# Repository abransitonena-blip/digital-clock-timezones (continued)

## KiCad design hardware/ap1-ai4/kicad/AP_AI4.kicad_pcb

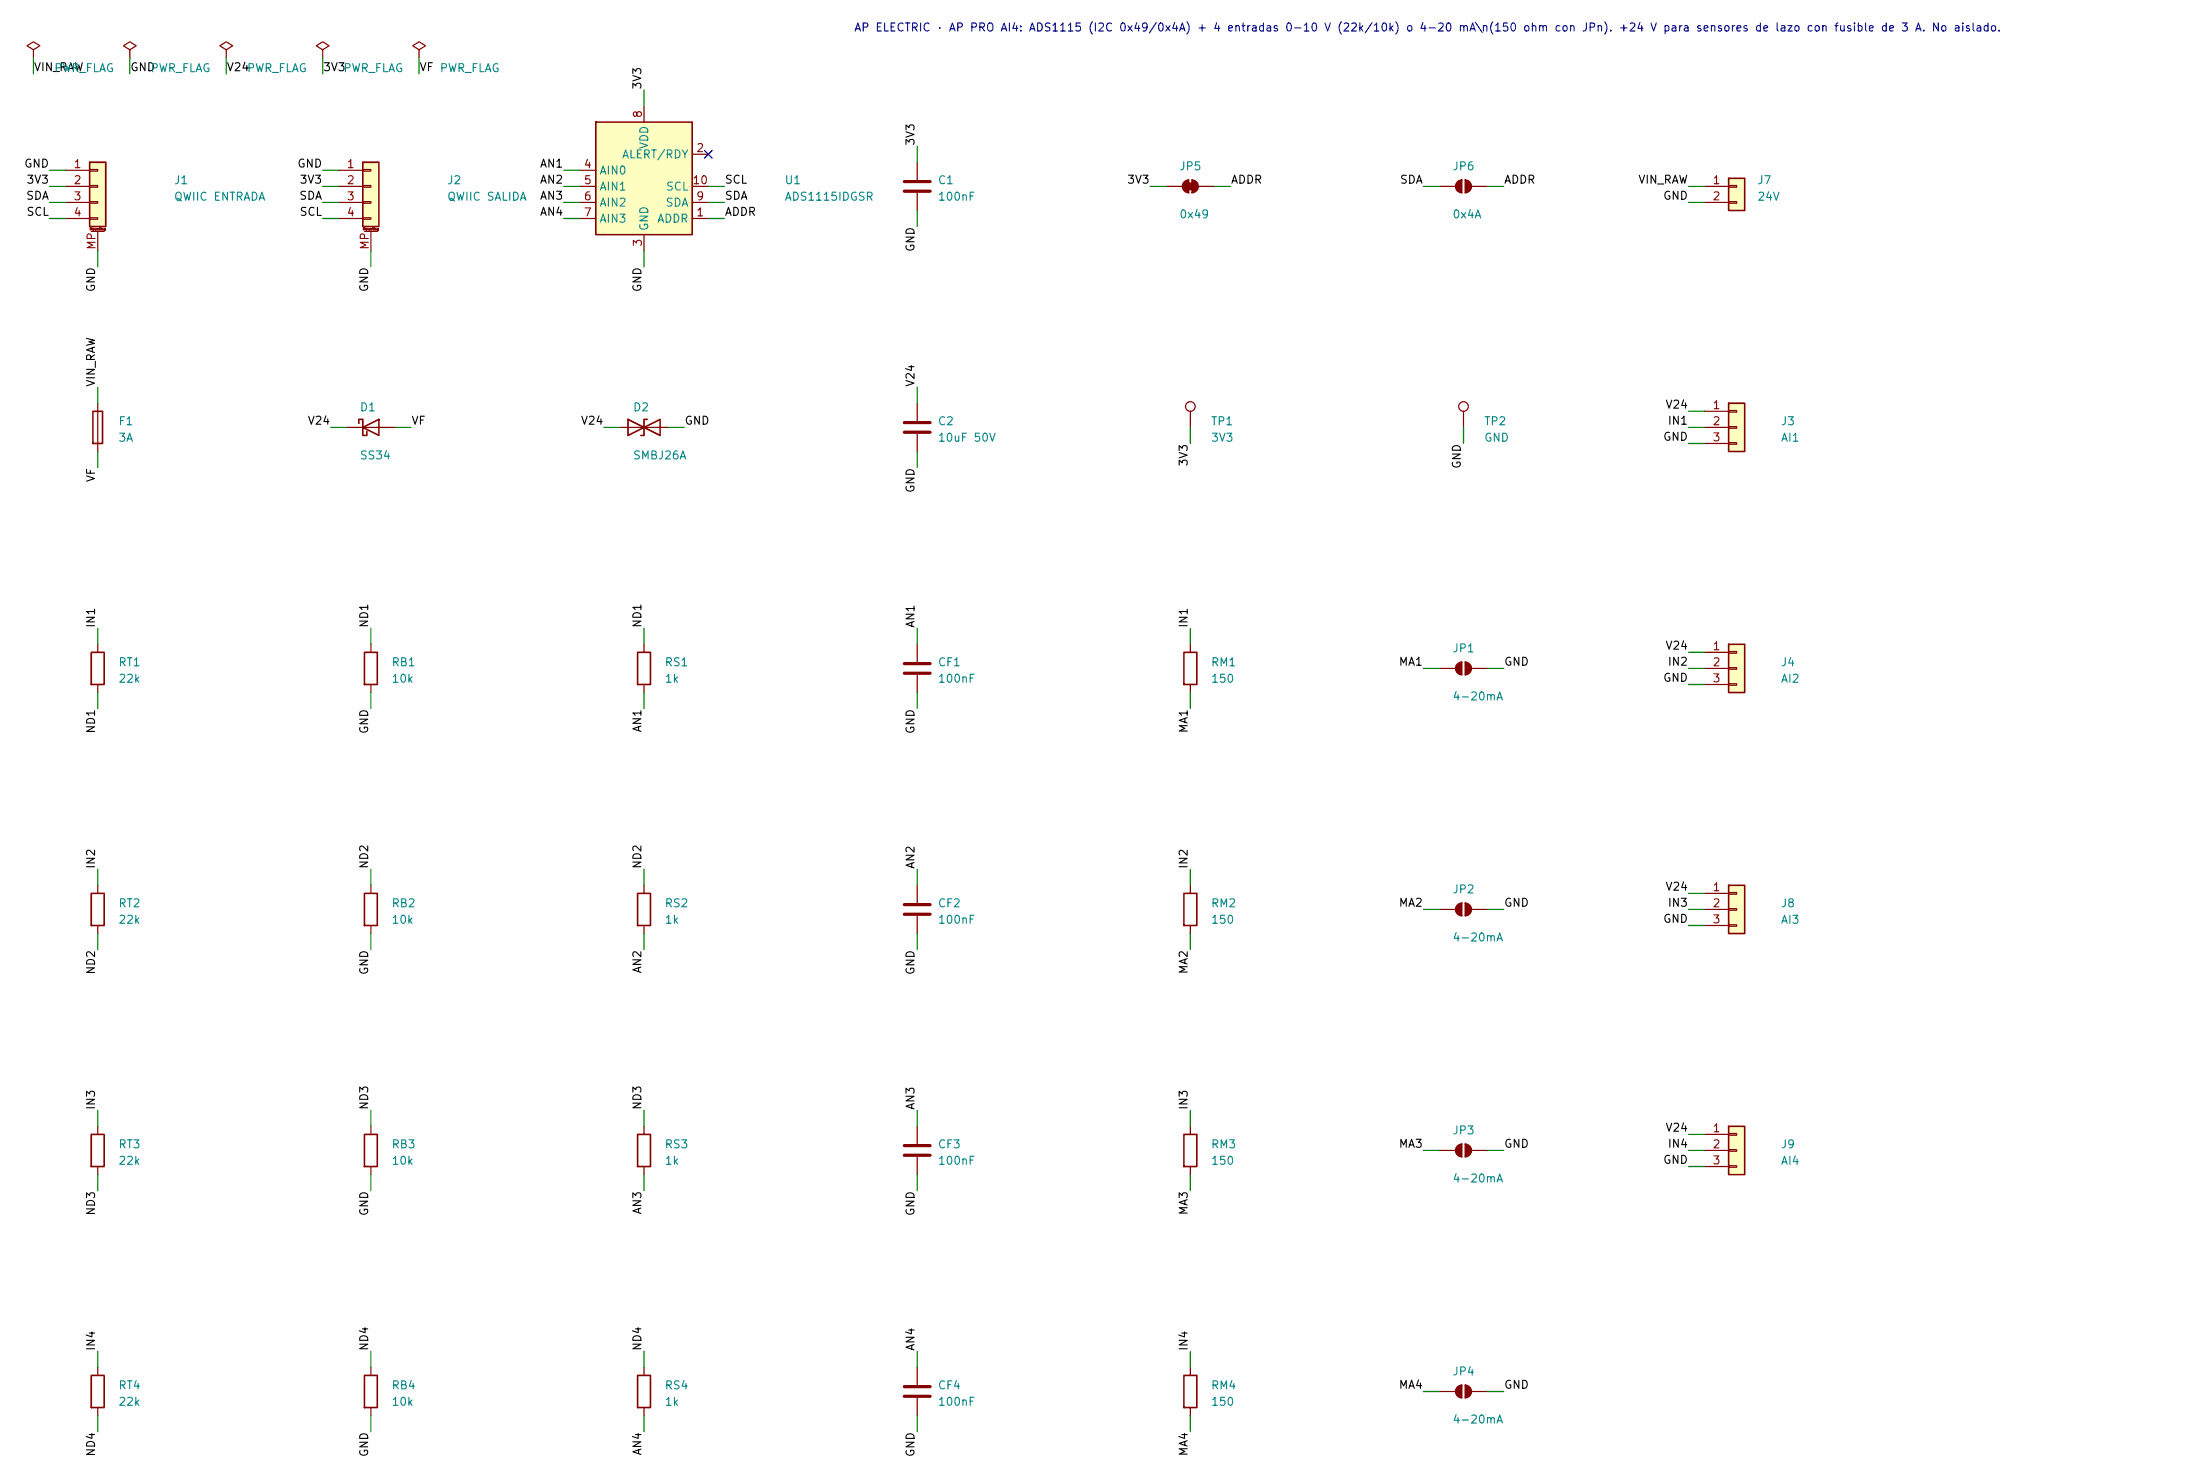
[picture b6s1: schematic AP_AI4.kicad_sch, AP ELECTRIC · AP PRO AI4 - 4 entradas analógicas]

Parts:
C1: 100nF; C_0603_1608Metric
C2: 10uF 50V; C_1206_3216Metric
CF1, CF2, CF3, CF4: 100nF; C_0603_1608Metric
D1: SS34; D_SMA
D2: SMBJ26A; D_SMB
F1: 3A; Fuse_1206_3216Metric
J1: QWIIC ENTRADA; JST_SH_SM04B-SRSS-TB_1x04-1MP_P1.00mm_Horizontal
J2: QWIIC SALIDA; JST_SH_SM04B-SRSS-TB_1x04-1MP_P1.00mm_Horizontal
J3: AI1; JST_XH_B3B-XH-A_1x03_P2.50mm_Vertical
J4: AI2; JST_XH_B3B-XH-A_1x03_P2.50mm_Vertical
J7: 24V; JST_VH_B2P-VH_1x02_P3.96mm_Vertical
J8: AI3; JST_XH_B3B-XH-A_1x03_P2.50mm_Vertical
J9: AI4; JST_XH_B3B-XH-A_1x03_P2.50mm_Vertical
JP1, JP2, JP3, JP4: 4-20mA; SolderJumper-2_P1.3mm_Open_RoundedPad1.0x1.5mm
JP5: 0x49; SolderJumper-2_P1.3mm_Bridged_RoundedPad1.0x1.5mm
JP6: 0x4A; SolderJumper-2_P1.3mm_Open_RoundedPad1.0x1.5mm
RB1, RB2, RB3, RB4: 10k; R_0603_1608Metric
RM1, RM2, RM3, RM4: 150; R_0805_2012Metric
RS1, RS2, RS3, RS4: 1k; R_0603_1608Metric
RT1, RT2, RT3, RT4: 22k; R_0603_1608Metric
TP1: 3V3; TestPoint_Pad_D1.5mm
TP2: GND; TestPoint_Pad_D1.5mm
U1: ADS1115IDGSR; TSSOP-10_3x3mm_P0.5mm

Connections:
/3V3: C1.1, J1.2, J2.2, JP5.1 (A), TP1.1, U1.8 (VDD)
/ADDR: JP5.2 (B), JP6.2 (B), U1.1 (ADDR)
/AN1: CF1.1, RS1.2, U1.4 (AIN0)
/AN2: CF2.1, RS2.2, U1.5 (AIN1)
/AN3: CF3.1, RS3.2, U1.6 (AIN2)
/AN4: CF4.1, RS4.2, U1.7 (AIN3)
/GND: C1.2, C2.2, CF1.2, CF2.2, CF3.2, CF4.2, D2.2 (A2), J1.1, J1.MP (MountPin), J2.1, J2.MP (MountPin), J3.3, J4.3, J7.2, J8.3, J9.3, JP1.2 (B), JP2.2 (B), JP3.2 (B), JP4.2 (B), RB1.2, RB2.2, RB3.2, RB4.2, TP2.1, U1.3 (GND)
/IN1: J3.2, RM1.1, RT1.1
/IN2: J4.2, RM2.1, RT2.1
/IN3: J8.2, RM3.1, RT3.1
/IN4: J9.2, RM4.1, RT4.1
/MA1: JP1.1 (A), RM1.2
/MA2: JP2.1 (A), RM2.2
/MA3: JP3.1 (A), RM3.2
/MA4: JP4.1 (A), RM4.2
/ND1: RB1.1, RS1.1, RT1.2
/ND2: RB2.1, RS2.1, RT2.2
/ND3: RB3.1, RS3.1, RT3.2
/ND4: RB4.1, RS4.1, RT4.2
/SCL: J1.4, J2.4, U1.10 (SCL)
/SDA: J1.3, J2.3, JP6.1 (A), U1.9 (SDA)
/V24: C2.1, D1.1 (K), D2.1 (A1), J3.1, J4.1, J8.1, J9.1
/VF: D1.2 (A), F1.2
/VIN_RAW: F1.1, J7.1

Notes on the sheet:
AP ELECTRIC · AP PRO AI4: ADS1115 (I2C 0x49/0x4A) + 4 entradas 0-10 V (22k/10k) o 4-20 mA\n(150 ohm con JPn). +24 V para sensores de lazo con fusible de 3 A. No aislado.

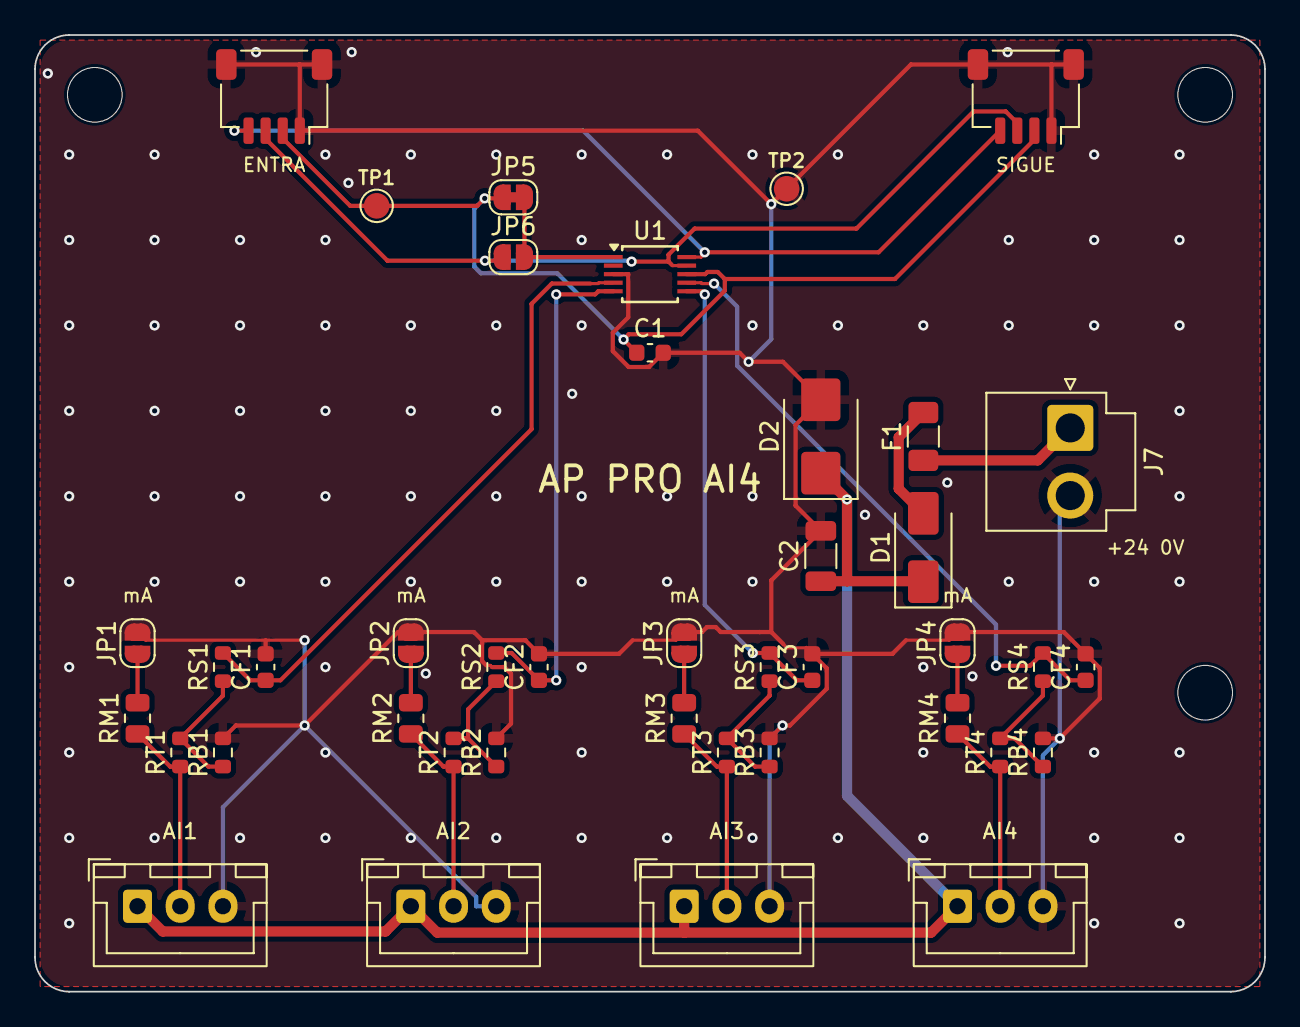
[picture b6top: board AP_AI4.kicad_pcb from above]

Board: 2 copper layers, 72.0 x 56.0 mm, 44 parts (0 on the bottom side), 24 nets.

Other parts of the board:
H1, H2, H3: MountingHole_3.2mm_M3

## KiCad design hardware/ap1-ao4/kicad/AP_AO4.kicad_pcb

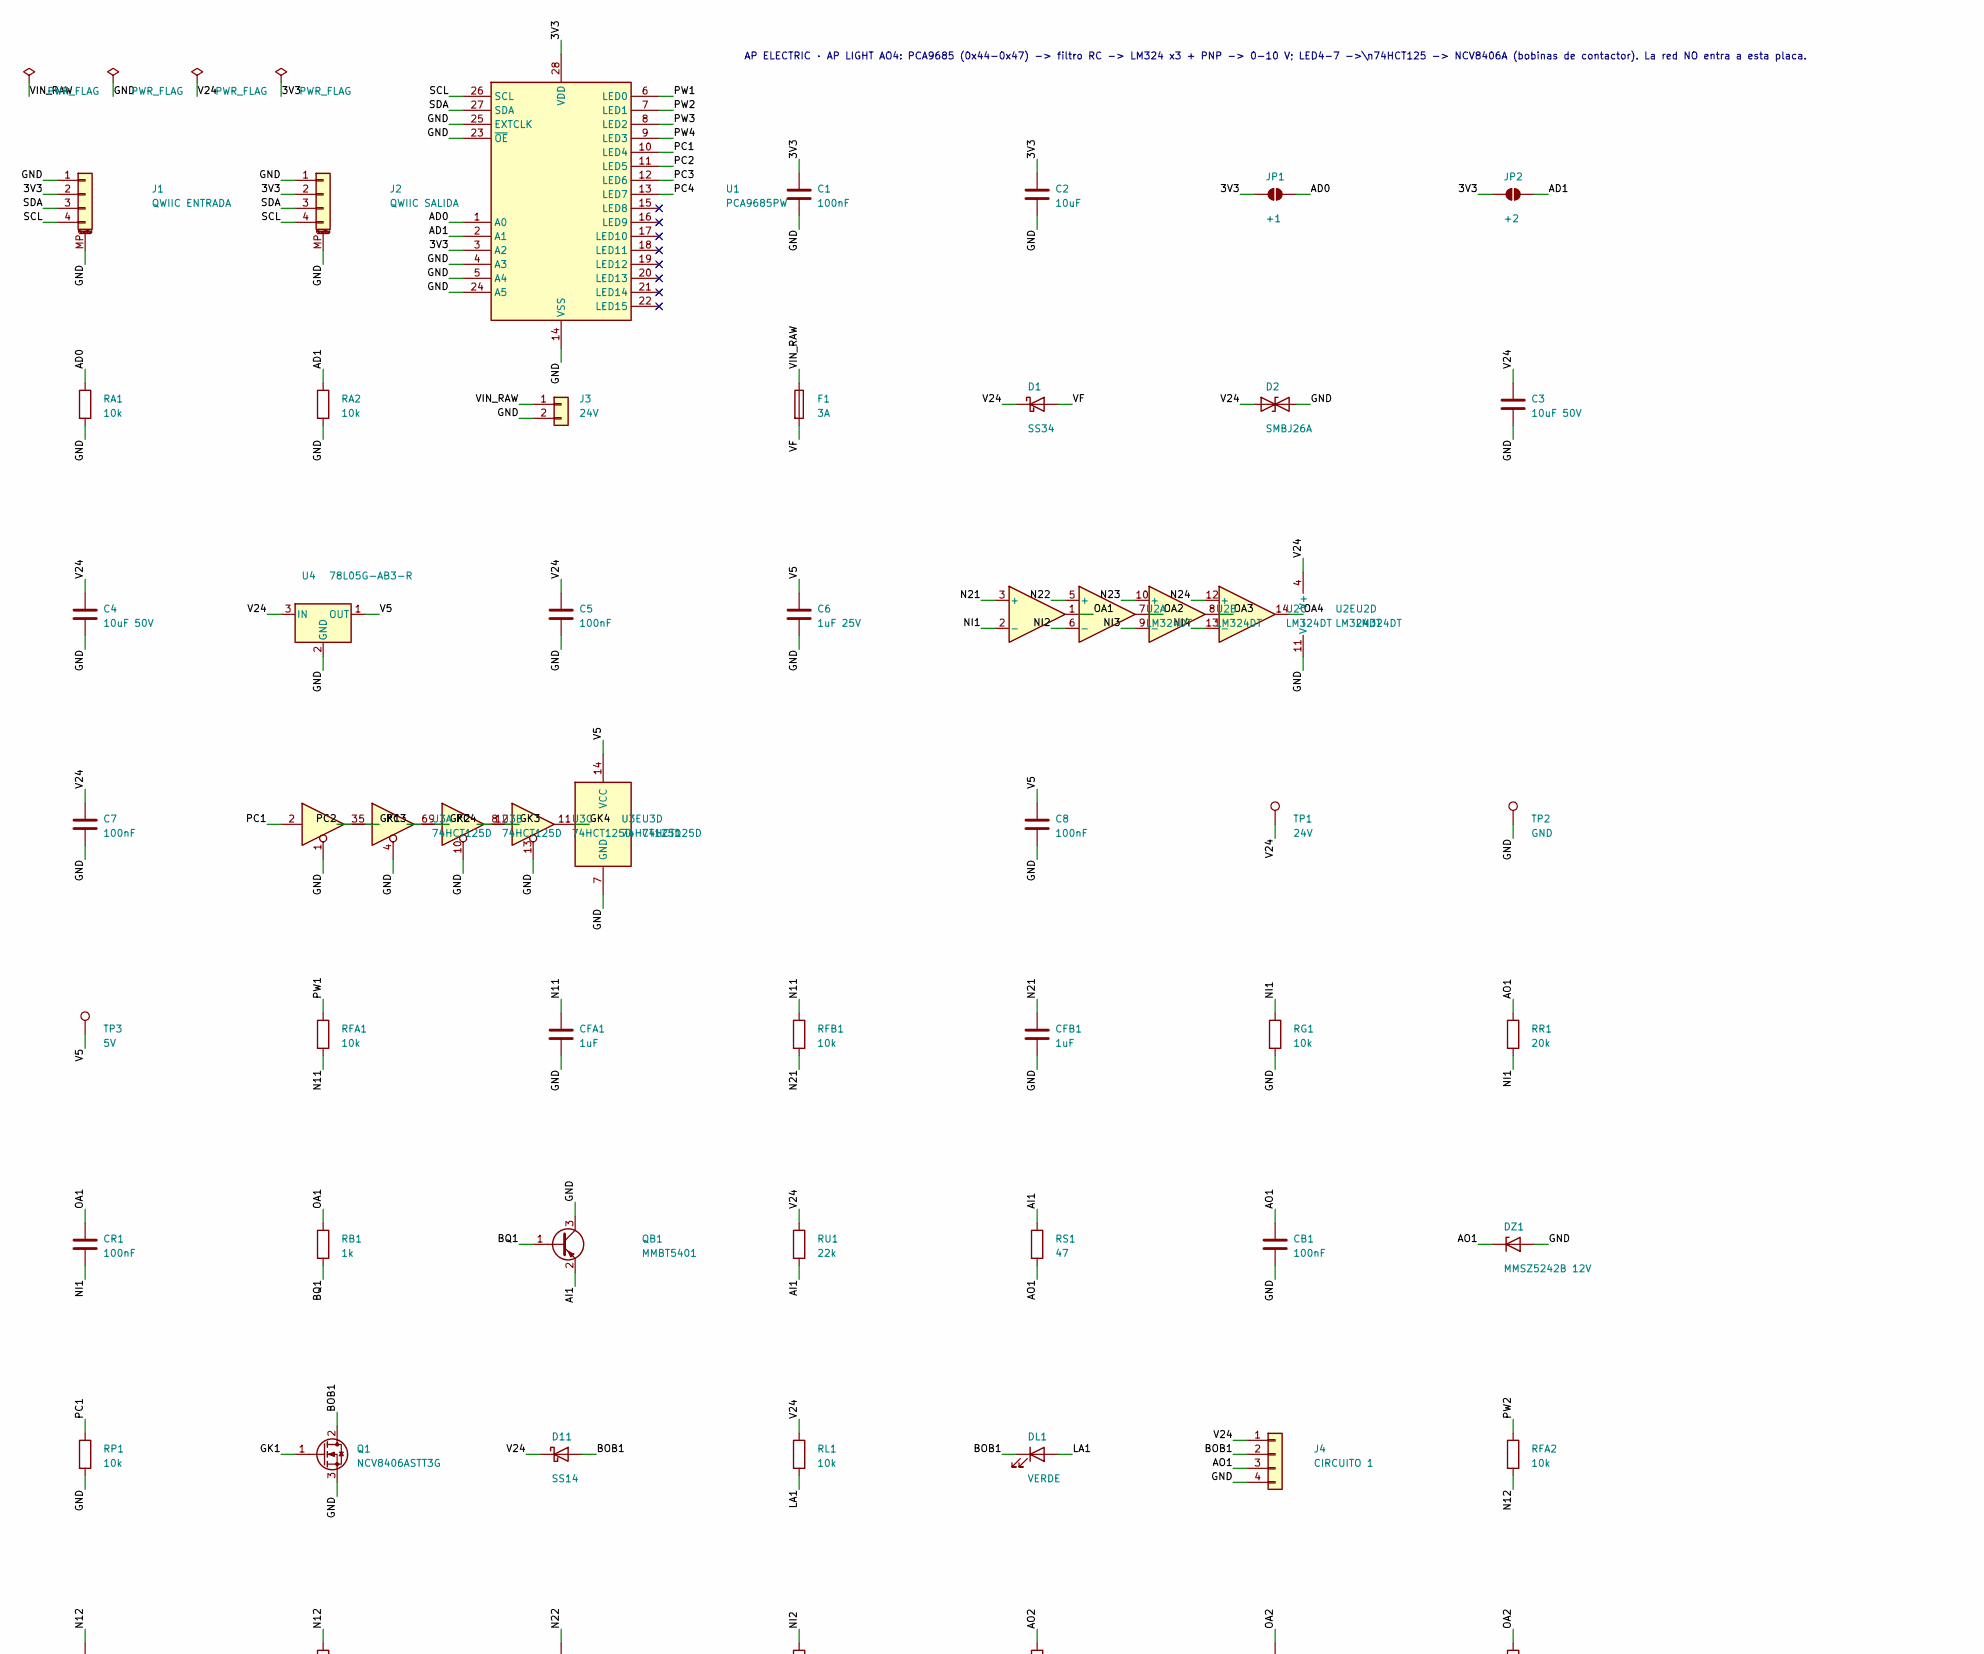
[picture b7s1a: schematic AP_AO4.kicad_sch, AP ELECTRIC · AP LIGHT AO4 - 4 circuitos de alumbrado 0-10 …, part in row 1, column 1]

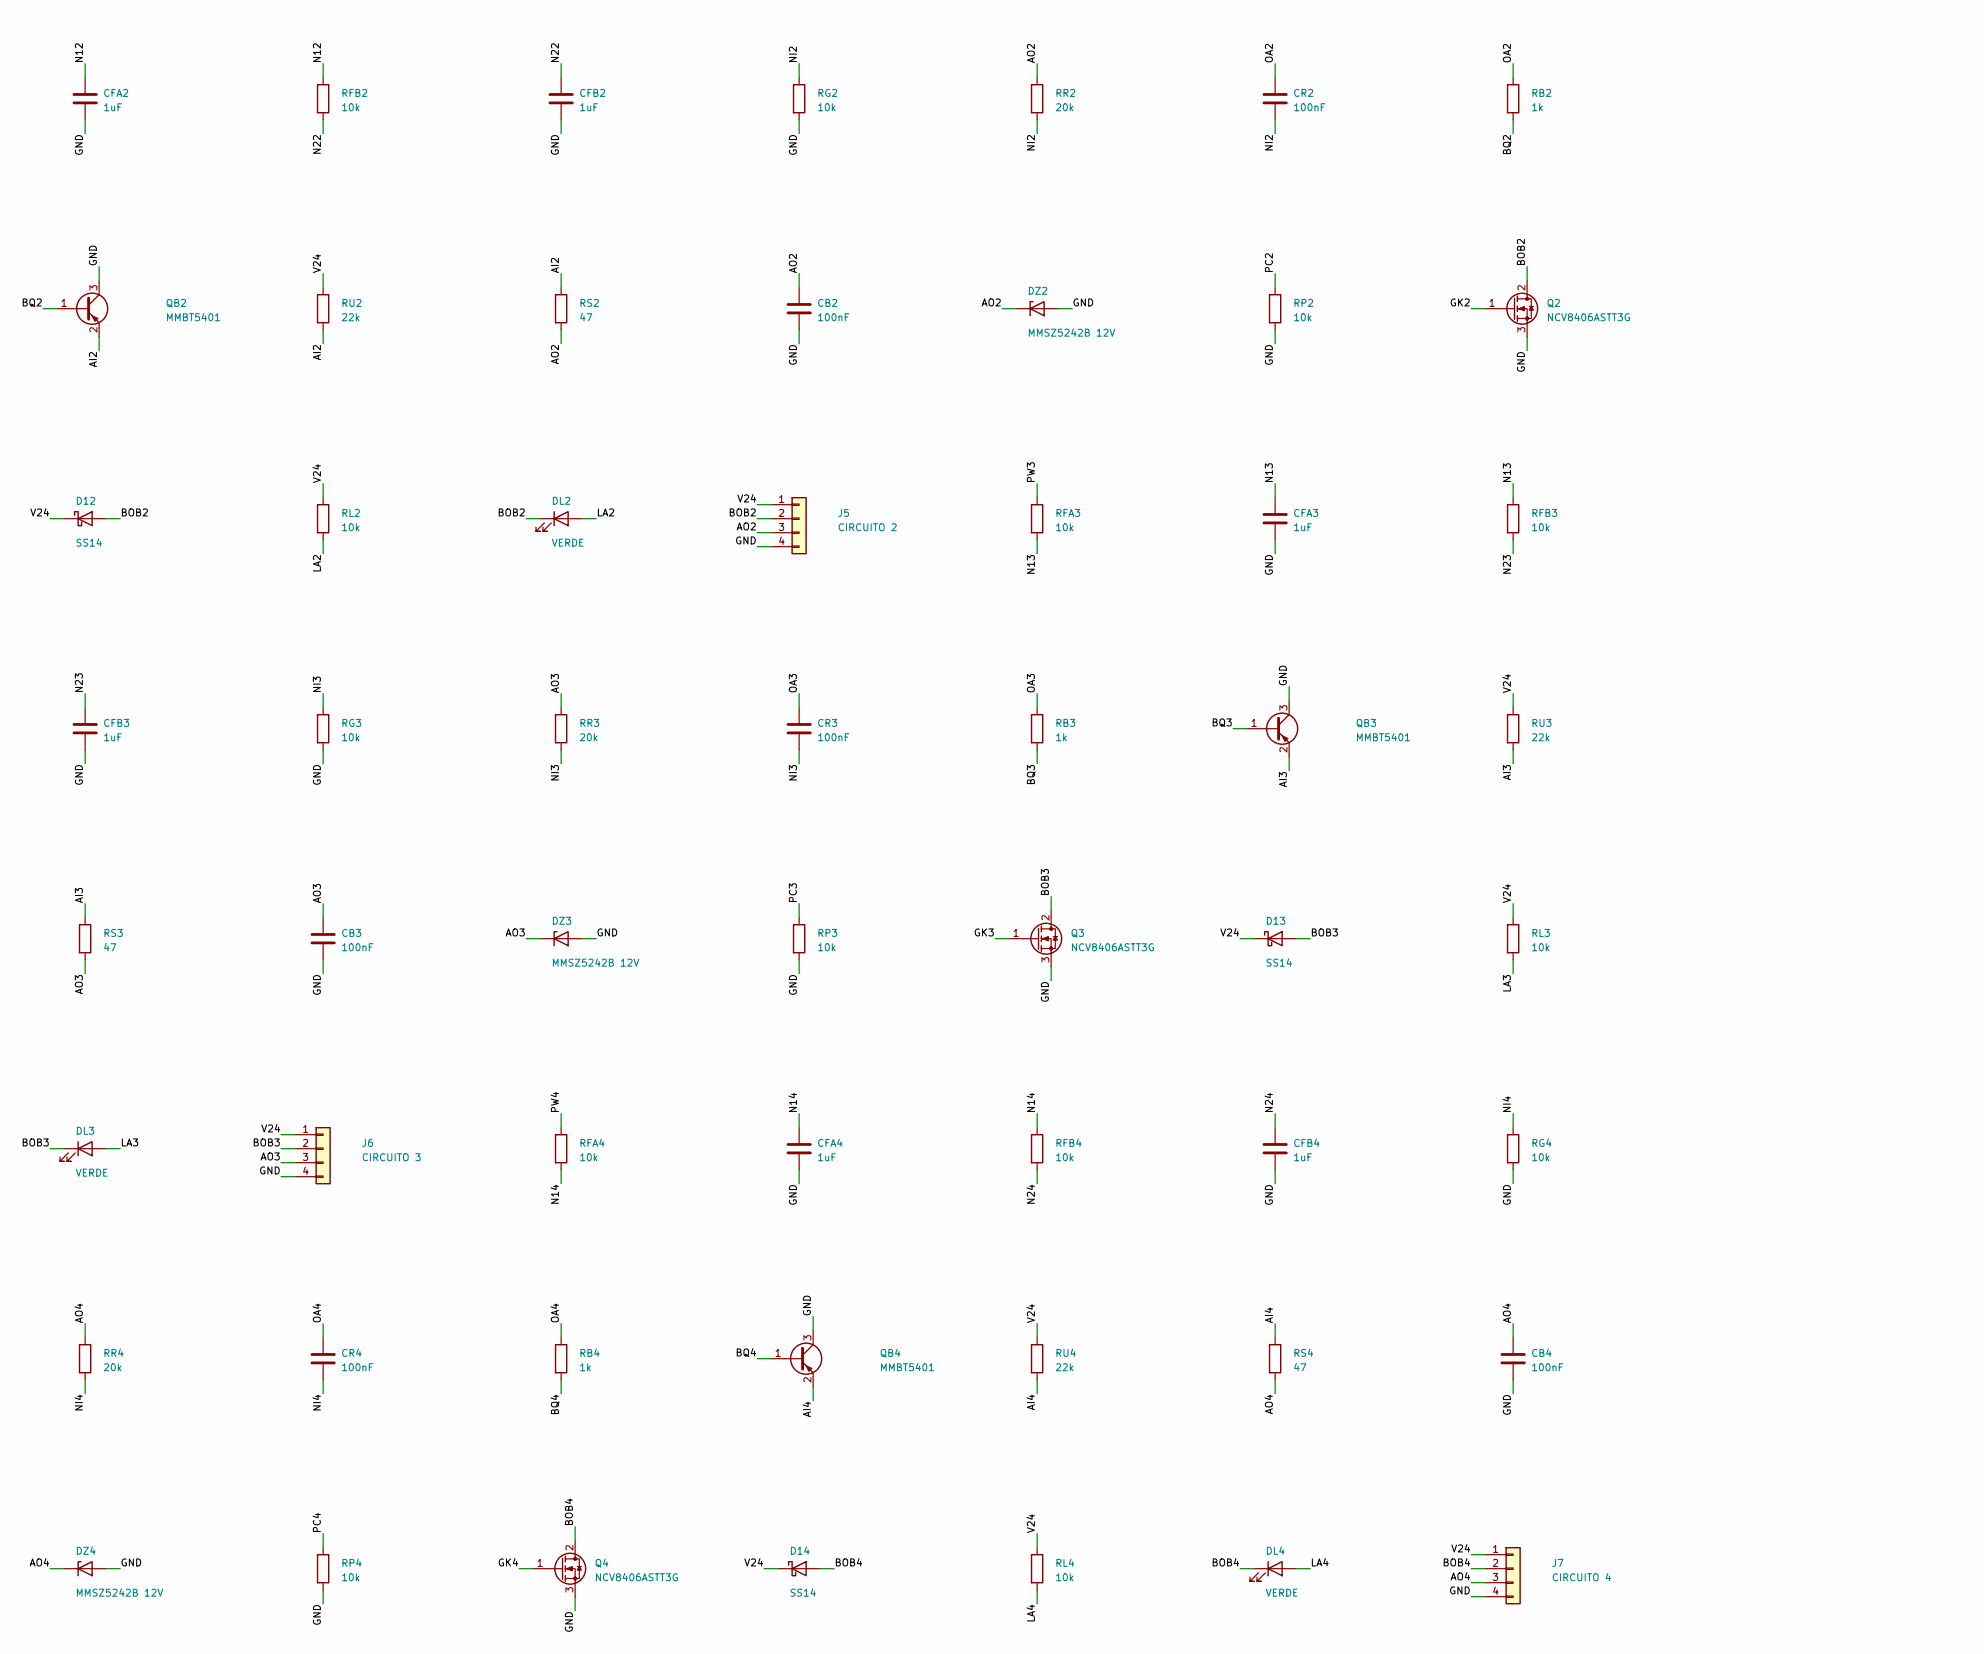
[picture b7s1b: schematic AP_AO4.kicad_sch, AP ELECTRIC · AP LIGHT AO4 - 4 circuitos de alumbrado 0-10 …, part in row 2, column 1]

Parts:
C1, C5, C7, C8: 100nF; C_0603_1608Metric
C2: 10uF; C_0805_2012Metric
C3, C4: 10uF 50V; C_1206_3216Metric
C6: 1uF 25V; C_0603_1608Metric
CB1, CB2, CB3, CB4: 100nF; C_0603_1608Metric
CFA1, CFA2, CFA3, CFA4: 1uF; C_0603_1608Metric
CFB1, CFB2, CFB3, CFB4: 1uF; C_0603_1608Metric
CR1, CR2, CR3, CR4: 100nF; C_0603_1608Metric
D1: SS34; D_SMA
D2: SMBJ26A; D_SMB
D11, D12, D13, D14: SS14; D_SMA
DL1, DL2, DL3, DL4: VERDE; LED_0603_1608Metric
DZ1, DZ2, DZ3, DZ4: MMSZ5242B 12V; D_SOD-123
F1: 3A; Fuse_1206_3216Metric
J1: QWIIC ENTRADA; JST_SH_SM04B-SRSS-TB_1x04-1MP_P1.00mm_Horizontal
J2: QWIIC SALIDA; JST_SH_SM04B-SRSS-TB_1x04-1MP_P1.00mm_Horizontal
J3: 24V; JST_VH_B2P-VH_1x02_P3.96mm_Vertical
J4: CIRCUITO 1; JST_XH_B4B-XH-A_1x04_P2.50mm_Vertical
J5: CIRCUITO 2; JST_XH_B4B-XH-A_1x04_P2.50mm_Vertical
J6: CIRCUITO 3; JST_XH_B4B-XH-A_1x04_P2.50mm_Vertical
J7: CIRCUITO 4; JST_XH_B4B-XH-A_1x04_P2.50mm_Vertical
JP1: +1; SolderJumper-2_P1.3mm_Open_RoundedPad1.0x1.5mm
JP2: +2; SolderJumper-2_P1.3mm_Open_RoundedPad1.0x1.5mm
Q1, Q2, Q3, Q4: NCV8406ASTT3G; SOT-223-3_TabPin2
QB1, QB2, QB3, QB4: MMBT5401; SOT-23
RA1, RA2: 10k; R_0603_1608Metric
RB1, RB2, RB3, RB4: 1k; R_0603_1608Metric
RFA1, RFA2, RFA3, RFA4: 10k; R_0603_1608Metric
RFB1, RFB2, RFB3, RFB4: 10k; R_0603_1608Metric
RG1, RG2, RG3, RG4: 10k; R_0603_1608Metric
RL1, RL2, RL3, RL4: 10k; R_0603_1608Metric
RP1, RP2, RP3, RP4: 10k; R_0603_1608Metric
RR1, RR2, RR3, RR4: 20k; R_0603_1608Metric
RS1, RS2, RS3, RS4: 47; R_0603_1608Metric
RU1, RU2, RU3, RU4: 22k; R_0603_1608Metric
TP1: 24V; TestPoint_Pad_D1.5mm
TP2: GND; TestPoint_Pad_D1.5mm
TP3: 5V; TestPoint_Pad_D1.5mm
U1: PCA9685PW; TSSOP-28_4.4x9.7mm_P0.65mm
U2: LM324DT; SOIC-14_3.9x8.7mm_P1.27mm
U3: 74HCT125D; SOIC-14_3.9x8.7mm_P1.27mm
U4: 78L05G-AB3-R; SOT-89-3

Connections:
/3V3: C1.1, C2.1, J1.2, J2.2, JP1.1 (A), JP2.1 (A), U1.3 (A2), U1.28 (VDD)
/AD0: JP1.2 (B), RA1.1, U1.1 (A0)
/AD1: JP2.2 (B), RA2.1, U1.2 (A1)
/AI1: QB1.2 (E), RS1.1, RU1.2
/AI2: QB2.2 (E), RS2.1, RU2.2
/AI3: QB3.2 (E), RS3.1, RU3.2
/AI4: QB4.2 (E), RS4.1, RU4.2
/AO1: CB1.1, DZ1.1 (K), J4.3, RR1.1, RS1.2
/AO2: CB2.1, DZ2.1 (K), J5.3, RR2.1, RS2.2
/AO3: CB3.1, DZ3.1 (K), J6.3, RR3.1, RS3.2
/AO4: CB4.1, DZ4.1 (K), J7.3, RR4.1, RS4.2
/BOB1: D11.2 (A), DL1.1 (K), J4.2, Q1.2 (D)
/BOB2: D12.2 (A), DL2.1 (K), J5.2, Q2.2 (D)
/BOB3: D13.2 (A), DL3.1 (K), J6.2, Q3.2 (D)
/BOB4: D14.2 (A), DL4.1 (K), J7.2, Q4.2 (D)
/BQ1: QB1.1 (B), RB1.2
/BQ2: QB2.1 (B), RB2.2
/BQ3: QB3.1 (B), RB3.2
/BQ4: QB4.1 (B), RB4.2
/GK1: Q1.1 (G), U3.3
/GK2: Q2.1 (G), U3.6
/GK3: Q3.1 (G), U3.8
/GK4: Q4.1 (G), U3.11
/GND: C1.2, C2.2, C3.2, C4.2, C5.2, C6.2, C7.2, C8.2, CB1.2, CB2.2, CB3.2, CB4.2, CFA1.2, CFA2.2, CFA3.2, CFA4.2, CFB1.2, CFB2.2, CFB3.2, CFB4.2, D2.2 (A2), DZ1.2 (A), DZ2.2 (A), DZ3.2 (A), DZ4.2 (A), J1.1, J1.MP (MountPin), J2.1, J2.MP (MountPin), J3.2, J4.4, J5.4, J6.4, J7.4, Q1.3 (S), Q2.3 (S), Q3.3 (S), Q4.3 (S), QB1.3 (C), QB2.3 (C), QB3.3 (C), QB4.3 (C), RA1.2, RA2.2, RG1.2, RG2.2, RG3.2, RG4.2, RP1.2, RP2.2, RP3.2, RP4.2, TP2.1, U1.4 (A3), U1.5 (A4), U1.14 (VSS), U1.23 (~OE), U1.24 (A5), U1.25 (EXTCLK), U2.11 (V-), U3.1, U3.4, U3.7 (GND), U3.10, U3.13, U4.2 (GND)
/LA1: DL1.2 (A), RL1.2
/LA2: DL2.2 (A), RL2.2
/LA3: DL3.2 (A), RL3.2
/LA4: DL4.2 (A), RL4.2
/N11: CFA1.1, RFA1.2, RFB1.1
/N12: CFA2.1, RFA2.2, RFB2.1
/N13: CFA3.1, RFA3.2, RFB3.1
/N14: CFA4.1, RFA4.2, RFB4.1
/N21: CFB1.1, RFB1.2, U2.3 (+)
/N22: CFB2.1, RFB2.2, U2.5 (+)
/N23: CFB3.1, RFB3.2, U2.10 (+)
/N24: CFB4.1, RFB4.2, U2.12 (+)
/NI1: CR1.2, RG1.1, RR1.2, U2.2 (-)
/NI2: CR2.2, RG2.1, RR2.2, U2.6 (-)
/NI3: CR3.2, RG3.1, RR3.2, U2.9 (-)
/NI4: CR4.2, RG4.1, RR4.2, U2.13 (-)
/OA1: CR1.1, RB1.1, U2.1
/OA2: CR2.1, RB2.1, U2.7
/OA3: CR3.1, RB3.1, U2.8
/OA4: CR4.1, RB4.1, U2.14
/PC1: RP1.1, U1.10 (LED4), U3.2
/PC2: RP2.1, U1.11 (LED5), U3.5
/PC3: RP3.1, U1.12 (LED6), U3.9
/PC4: RP4.1, U1.13 (LED7), U3.12
/PW1: RFA1.1, U1.6 (LED0)
/PW2: RFA2.1, U1.7 (LED1)
/PW3: RFA3.1, U1.8 (LED2)
/PW4: RFA4.1, U1.9 (LED3)
/SCL: J1.4, J2.4, U1.26 (SCL)
/SDA: J1.3, J2.3, U1.27 (SDA)
/V5: C6.1, C8.1, TP3.1, U3.14 (VCC), U4.1 (OUT)
/V24: C3.1, C4.1, C5.1, C7.1, D1.1 (K), D2.1 (A1), D11.1 (K), D12.1 (K), D13.1 (K), D14.1 (K), J4.1, J5.1, J6.1, J7.1, RL1.1, RL2.1, RL3.1, RL4.1, RU1.1, RU2.1, RU3.1, RU4.1, TP1.1, U2.4 (V+), U4.3 (IN)
/VF: D1.2 (A), F1.2
/VIN_RAW: F1.1, J3.1

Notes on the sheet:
AP ELECTRIC · AP LIGHT AO4: PCA9685 (0x44-0x47) -> filtro RC -> LM324 x3 + PNP -> 0-10 V; LED4-7 ->\n74HCT125 -> NCV8406A (bobinas de contactor). La red NO entra a esta placa.

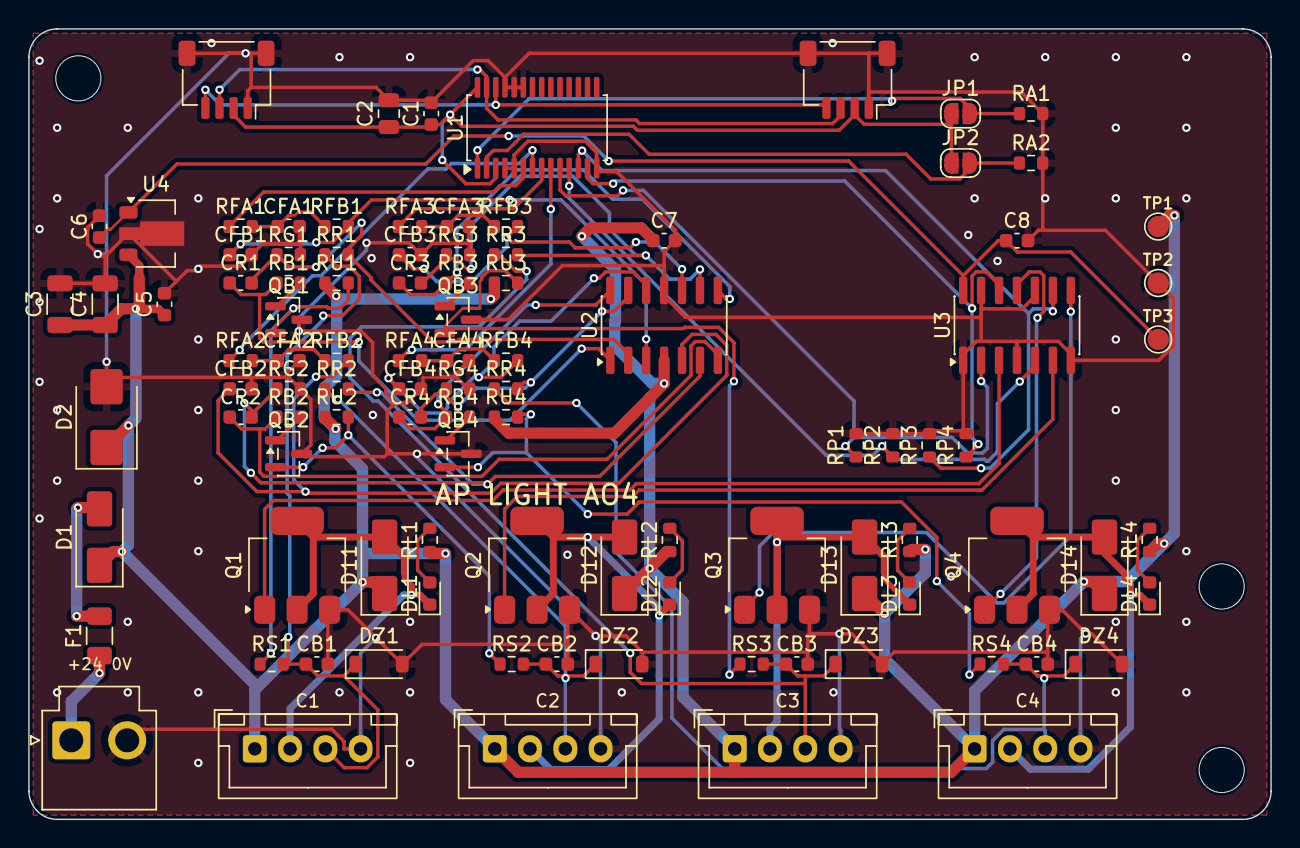
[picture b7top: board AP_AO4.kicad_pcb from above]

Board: 2 copper layers, 88.0 x 56.0 mm, 104 parts (0 on the bottom side), 58 nets.

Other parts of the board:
H1, H2, H3: MountingHole_3.2mm_M3

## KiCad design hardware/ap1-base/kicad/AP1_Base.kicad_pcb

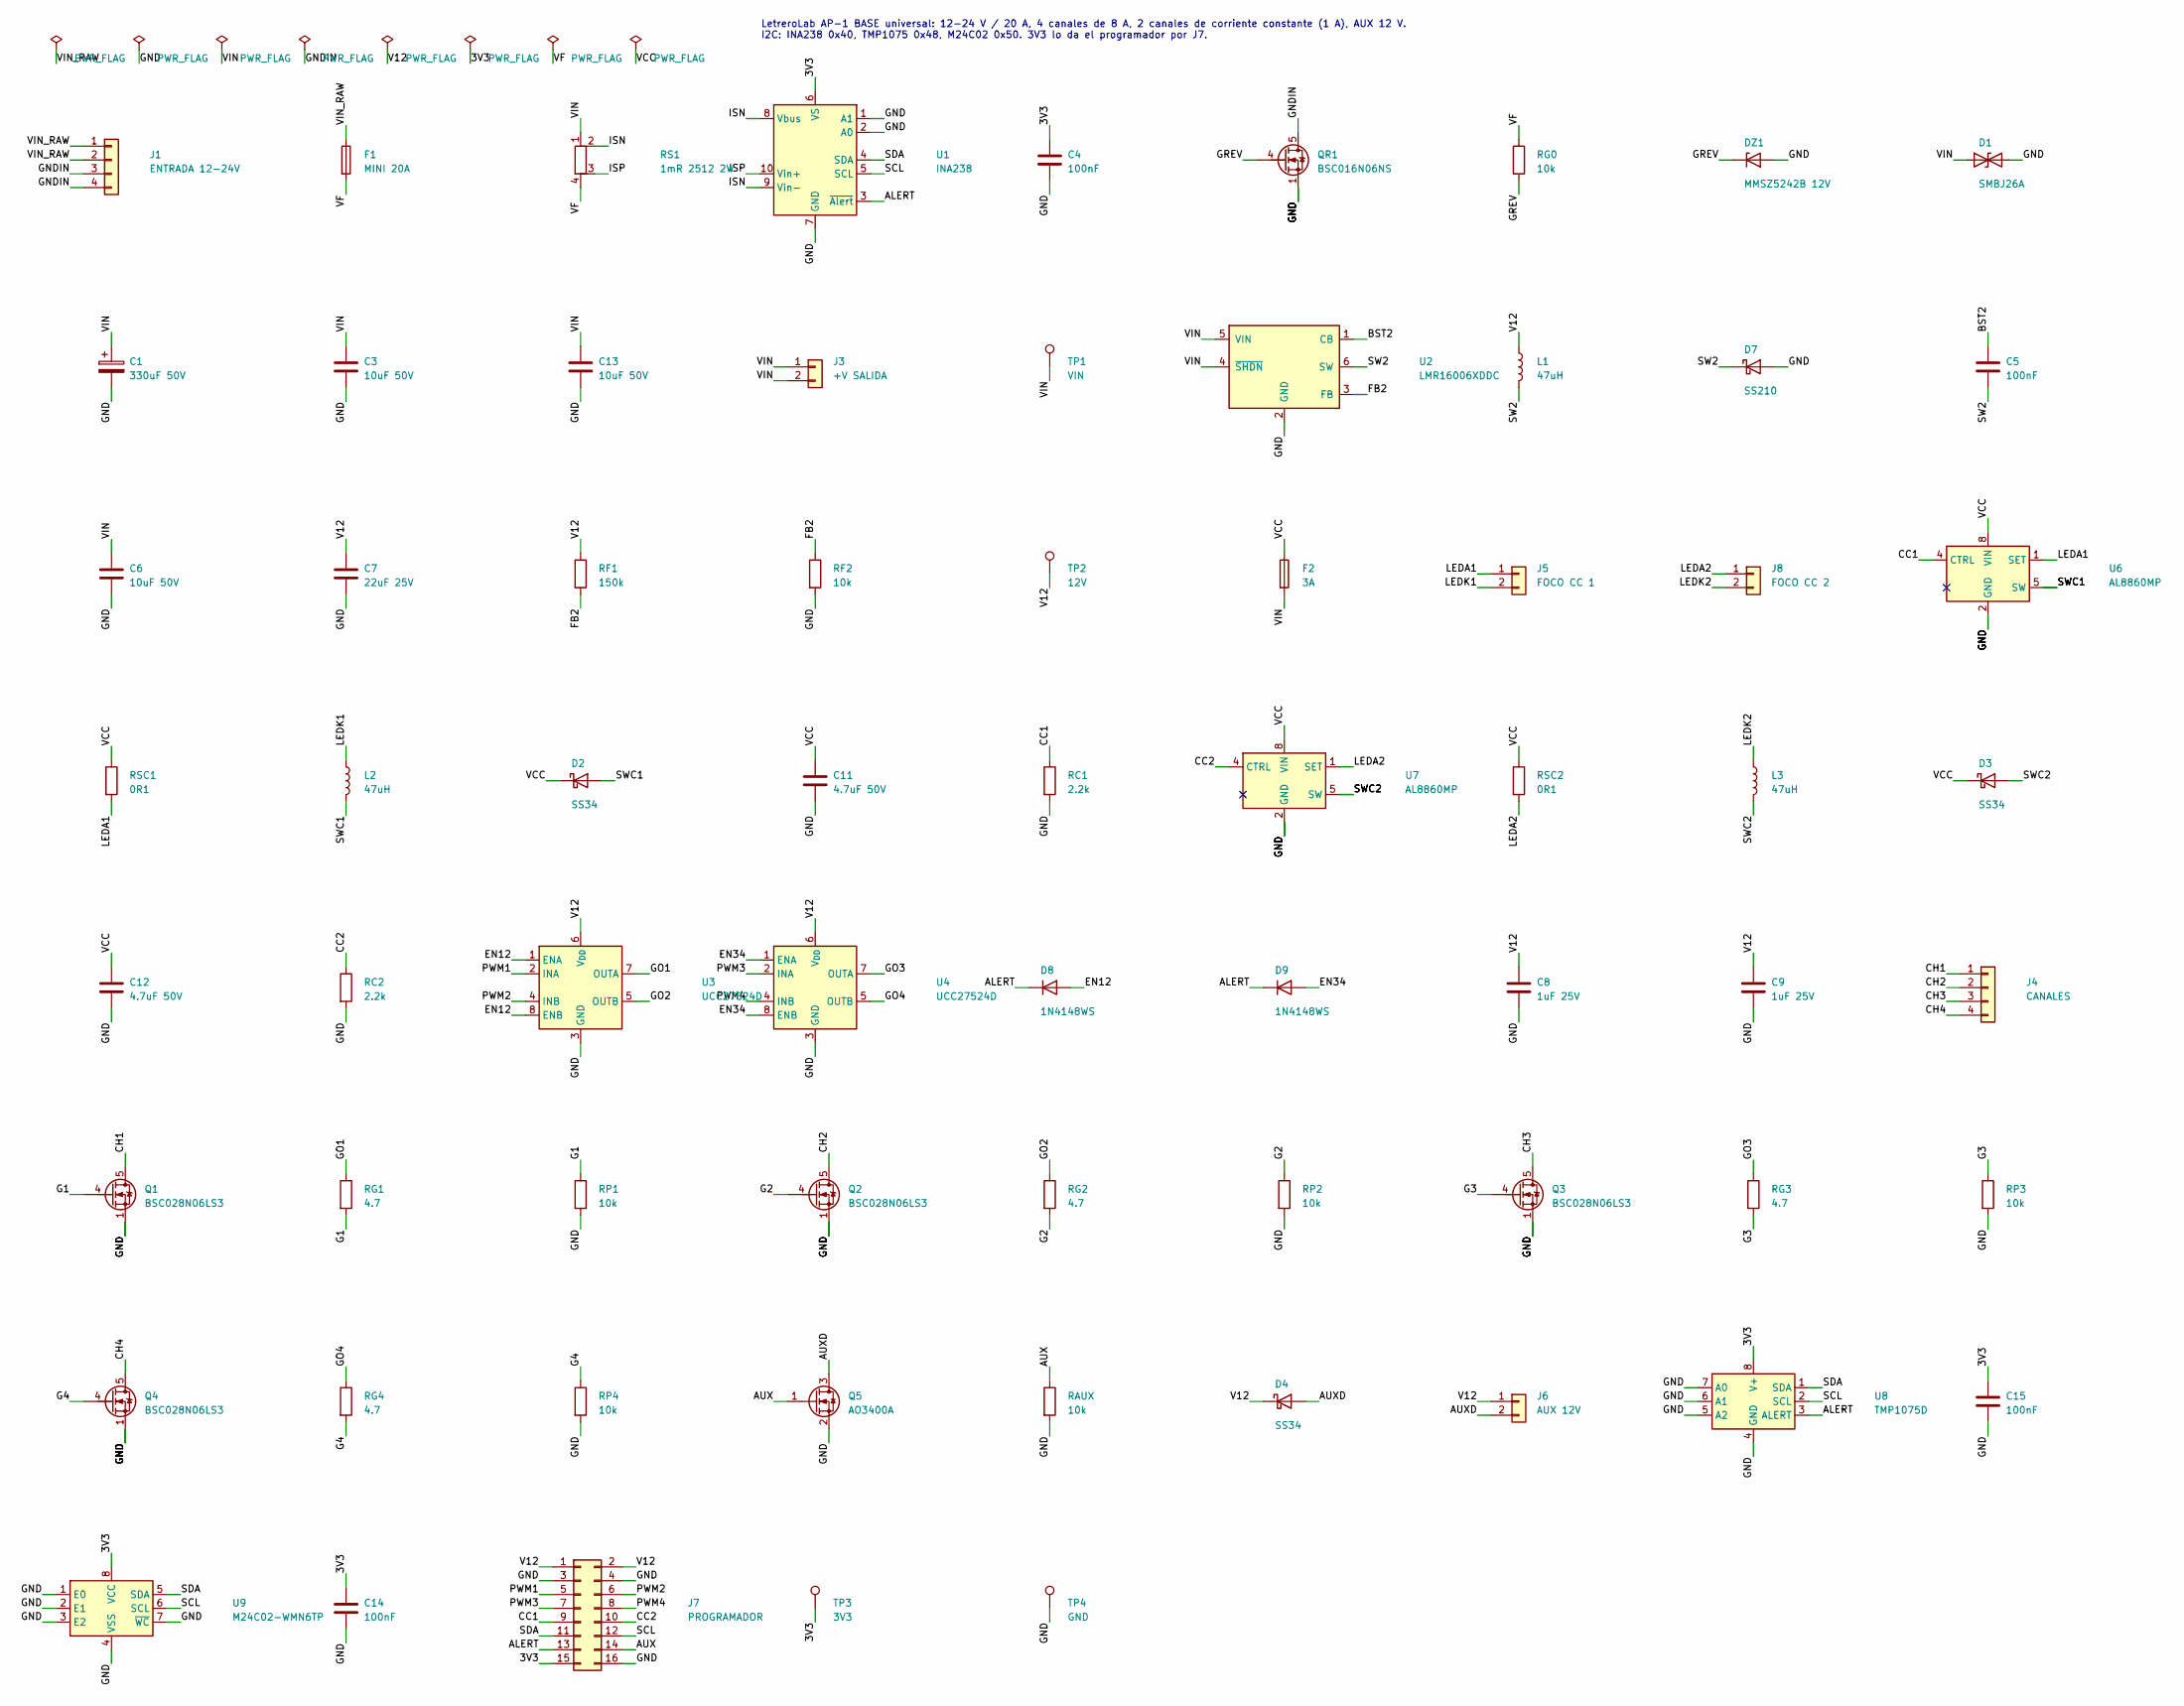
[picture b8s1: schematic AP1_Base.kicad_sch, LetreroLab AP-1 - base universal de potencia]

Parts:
C1: 330uF 50V; CP_Elec_10x10.5
C3, C6, C13: 10uF 50V; C_1206_3216Metric
C4, C5, C14, C15: 100nF; C_0603_1608Metric
C7: 22uF 25V; C_1206_3216Metric
C8, C9: 1uF 25V; C_0603_1608Metric
C11, C12: 4.7uF 50V; C_1206_3216Metric
D1: SMBJ26A; D_SMB
D2, D3, D4: SS34; D_SMA
D7: SS210; D_SMA
D8, D9: 1N4148WS; D_SOD-323
DZ1: MMSZ5242B 12V; D_SOD-123
F1: MINI 20A; Fuseholder_Blade_Mini_Keystone_3568
F2: 3A; Fuse_1206_3216Metric
J1: ENTRADA 12-24V; JST_VH_B4P-VH_1x04_P3.96mm_Vertical
J3: +V SALIDA; JST_VH_B2P-VH_1x02_P3.96mm_Vertical
J4: CANALES; JST_VH_B4P-VH_1x04_P3.96mm_Vertical
J5: FOCO CC 1; JST_XH_B2B-XH-A_1x02_P2.50mm_Vertical
J6: AUX 12V; JST_XH_B2B-XH-A_1x02_P2.50mm_Vertical
J7: PROGRAMADOR; PinSocket_2x08_P2.54mm_Vertical
J8: FOCO CC 2; JST_XH_B2B-XH-A_1x02_P2.50mm_Vertical
L1: 47uH; L_Changjiang_FNR4030S
L2, L3: 47uH; L_Changjiang_FNR6045S
Q1, Q2, Q3, Q4: BSC028N06LS3; TDSON-8-1
Q5: AO3400A; SOT-23
QR1: BSC016N06NS; TDSON-8-1
RAUX: 10k; R_0603_1608Metric
RC1, RC2: 2.2k; R_0603_1608Metric
RF1: 150k; R_0603_1608Metric
RF2: 10k; R_0603_1608Metric
RG0: 10k; R_0603_1608Metric
RG1, RG2, RG3, RG4: 4.7; R_0603_1608Metric
RP1, RP2, RP3, RP4: 10k; R_0603_1608Metric
RS1: 1mR 2512 2W; R_2512_Kelvin_NetTie
RSC1, RSC2: 0R1; R_1206_3216Metric
TP1: VIN; TestPoint_Pad_D1.5mm
TP2: 12V; TestPoint_Pad_D1.5mm
TP3: 3V3; TestPoint_Pad_D1.5mm
TP4: GND; TestPoint_Pad_D1.5mm
U1: INA238; VSSOP-10_3x3mm_P0.5mm
U2: LMR16006XDDC; SOT-23-6
U3, U4: UCC27524D; SOIC-8_3.9x4.9mm_P1.27mm
U6, U7: AL8860MP; MSOP-8-1EP_3x3mm_P0.65mm_EP1.5x1.8mm
U8: TMP1075D; SOIC-8_3.9x4.9mm_P1.27mm
U9: M24C02-WMN6TP; SOIC-8_3.9x4.9mm_P1.27mm

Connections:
/3V3: C4.1, C14.1, C15.1, J7.15, TP3.1, U1.6 (VS), U8.8 (V+), U9.8 (VCC)
/ALERT: D8.1 (K), D9.1 (K), J7.13, U1.3 (~Alert), U8.3 (ALERT)
/AUX: J7.14, Q5.1 (G), RAUX.1
/AUXD: D4.2 (A), J6.2, Q5.3 (D)
/BST2: C5.1, U2.1 (CB)
/CC1: J7.9, RC1.1, U6.4 (CTRL)
/CC2: J7.10, RC2.1, U7.4 (CTRL)
/CH1: J4.1, Q1.5 (D)
/CH2: J4.2, Q2.5 (D)
/CH3: J4.3, Q3.5 (D)
/CH4: J4.4, Q4.5 (D)
/EN12: D8.2 (A), U3.1 (ENA), U3.8 (ENB)
/EN34: D9.2 (A), U4.1 (ENA), U4.8 (ENB)
/FB2: RF1.2, RF2.1, U2.3 (FB)
/G1: Q1.4 (G), RG1.2, RP1.1
/G2: Q2.4 (G), RG2.2, RP2.1
/G3: Q3.4 (G), RG3.2, RP3.1
/G4: Q4.4 (G), RG4.2, RP4.1
/GND: C1.2, C3.2, C4.2, C6.2, C7.2, C8.2, C9.2, C11.2, C12.2, C13.2, C14.2, C15.2, D1.2 (A2), D7.2 (A), DZ1.2 (A), J7.3, J7.4, J7.16, Q1.1 (S), Q1.2 (S), Q1.3 (S), Q2.1 (S), Q2.2 (S), Q2.3 (S), Q3.1 (S), Q3.2 (S), Q3.3 (S), Q4.1 (S), Q4.2 (S), Q4.3 (S), Q5.2 (S), QR1.1 (S), QR1.2 (S), QR1.3 (S), RAUX.2, RC1.2, RC2.2, RF2.2, RP1.2, RP2.2, RP3.2, RP4.2, TP4.1, U1.1 (A1), U1.2 (A0), U1.7 (GND), U2.2 (GND), U3.3 (GND), U4.3 (GND), U6.2 (GND), U6.3 (GND), U6.9 (GND), U7.2 (GND), U7.3 (GND), U7.9 (GND), U8.4 (GND), U8.5 (A2), U8.6 (A1), U8.7 (A0), U9.1 (E0), U9.2 (E1), U9.3 (E2), U9.4 (VSS), U9.7 (~WC)
/GNDIN: J1.3, J1.4, QR1.5 (D)
/GO1: RG1.1, U3.7 (OUTA)
/GO2: RG2.1, U3.5 (OUTB)
/GO3: RG3.1, U4.7 (OUTA)
/GO4: RG4.1, U4.5 (OUTB)
/GREV: DZ1.1 (K), QR1.4 (G), RG0.2
/ISN: RS1.2, U1.8 (Vbus), U1.9 (Vin-)
/ISP: RS1.3, U1.10 (Vin+)
/LEDA1: J5.1, RSC1.2, U6.1 (SET)
/LEDA2: J8.1, RSC2.2, U7.1 (SET)
/LEDK1: J5.2, L2.1
/LEDK2: J8.2, L3.1
/PWM1: J7.5, U3.2 (INA)
/PWM2: J7.6, U3.4 (INB)
/PWM3: J7.7, U4.2 (INA)
/PWM4: J7.8, U4.4 (INB)
/SCL: J7.12, U1.5 (SCL), U8.2 (SCL), U9.6 (SCL)
/SDA: J7.11, U1.4 (SDA), U8.1 (SDA), U9.5 (SDA)
/SW2: C5.2, D7.1 (K), L1.2, U2.6 (SW)
/SWC1: D2.2 (A), L2.2, U6.5 (SW), U6.6 (SW)
/SWC2: D3.2 (A), L3.2, U7.5 (SW), U7.6 (SW)
/V12: C7.1, C8.1, C9.1, D4.1 (K), J6.1, J7.1, J7.2, L1.1, RF1.1, TP2.1, U3.6 (V_{DD}), U4.6 (V_{DD})
/VCC: C11.1, C12.1, D2.1 (K), D3.1 (K), F2.1, RSC1.1, RSC2.1, U6.8 (VIN), U7.8 (VIN)
/VF: F1.2, RG0.1, RS1.4
/VIN: C1.1, C3.1, C6.1, C13.1, D1.1 (A1), F2.2, J3.1, J3.2, RS1.1, TP1.1, U2.4 (~SHDN), U2.5 (VIN)
/VIN_RAW: F1.1, J1.1, J1.2

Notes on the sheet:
LetreroLab AP-1 BASE universal: 12-24 V / 20 A, 4 canales de 8 A, 2 canales de corriente constante (1 A), AUX 12 V. I2C: INA238 0x40, TMP1075 0x48, M24C02 0x50. 3V3 lo da el programador por J7.
